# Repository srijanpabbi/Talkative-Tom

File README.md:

# Talkative-Tom
GOTO: https://srijanpabbi.in/projects/#topic_tt
Doc: https://srijanpabbi.blogspot.com/2020/01/talkative-tom.html
Audio storing &amp; playback device with pitch modification using MSP-430 TI-microcontroller / Atmega328P microcontroller, SPI Serial Flash for Storage &amp; class-D amplifier for speaker

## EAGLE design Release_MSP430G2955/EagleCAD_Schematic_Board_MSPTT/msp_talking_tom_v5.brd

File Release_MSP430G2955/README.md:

This is the MSP430 version of this project. For full documentation on Atmega version visit https://srijanpabbi.blogspot.com/2020/01/talkative-tom.html

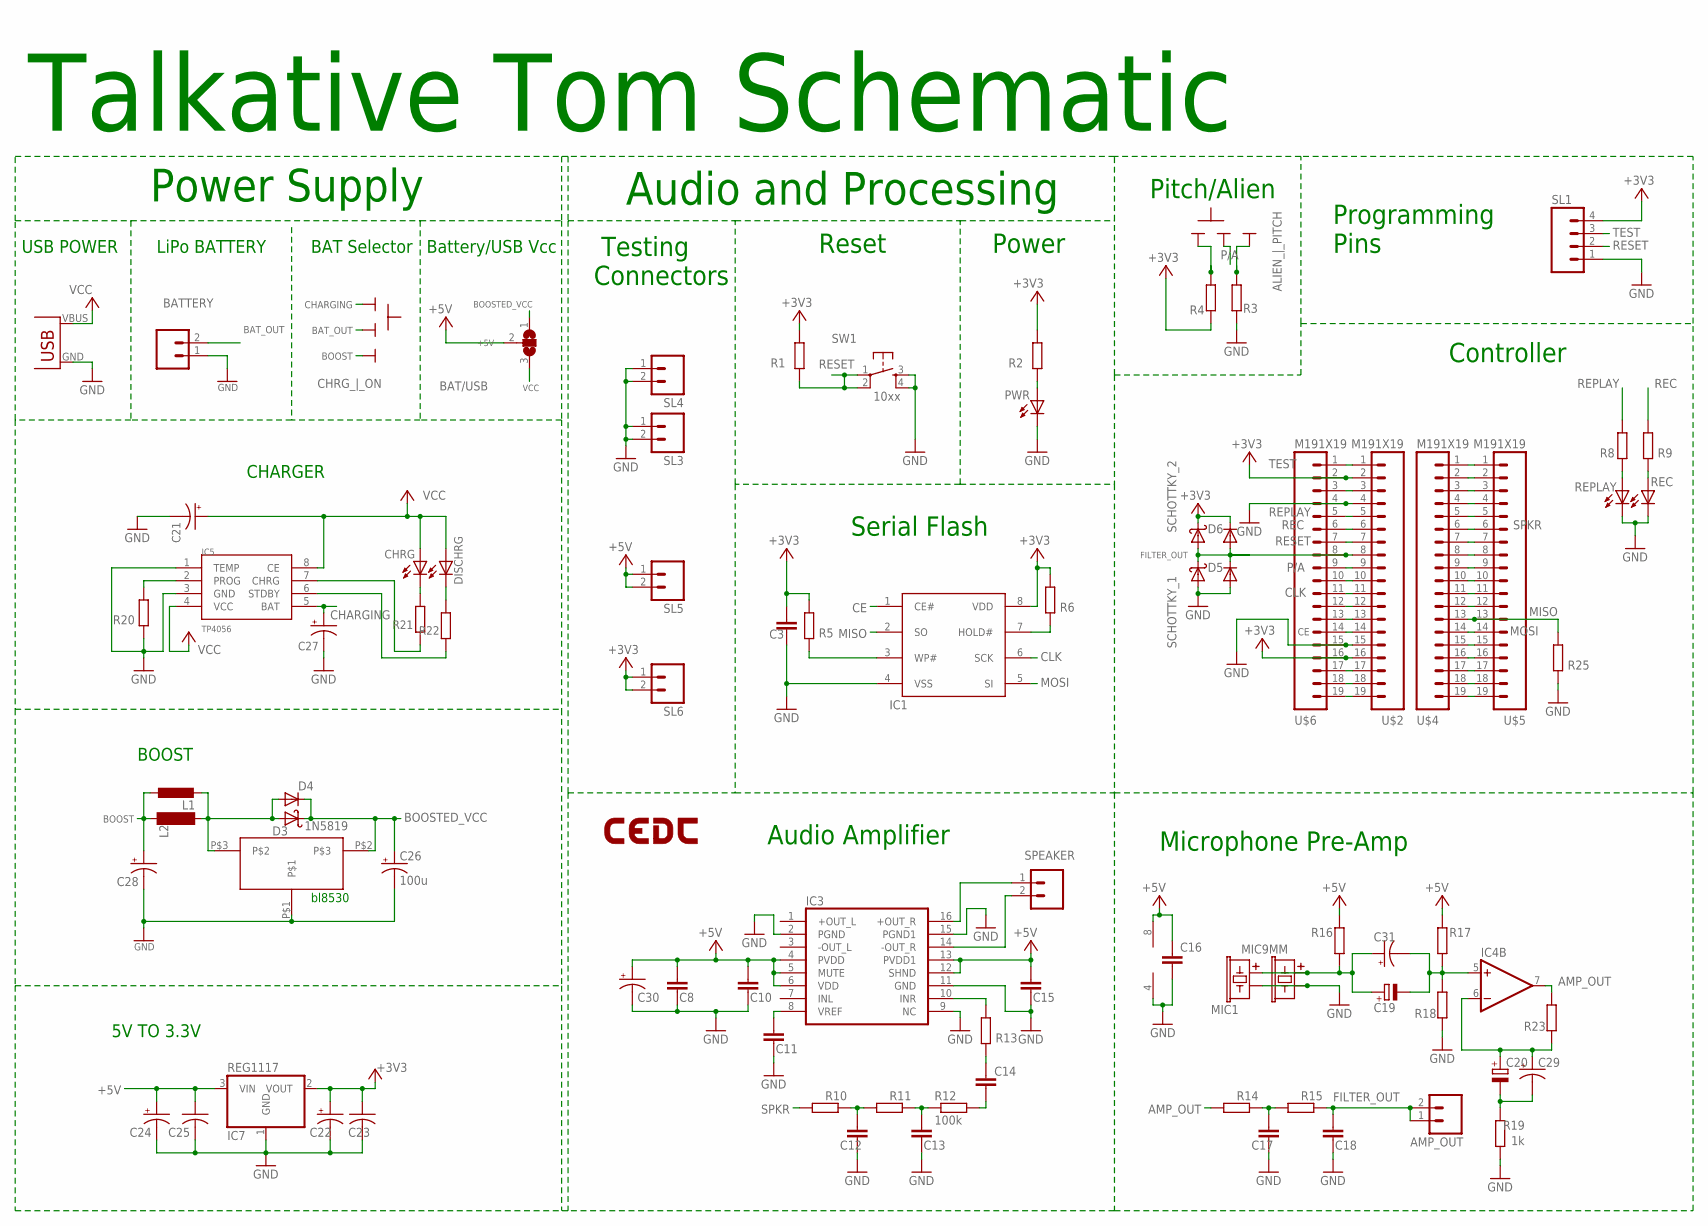
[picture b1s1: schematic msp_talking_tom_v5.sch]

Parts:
ALIEN_|_PITCH: SLIDESWITCH-BIG; BIGSWITCH
AMP_OUT: M02; 02P
BAT/USB: SJ2W; SJ_2
BATTERY: M02JST-PTH-2; 02P
C3, C12, C16, C17, C18, C23, C25: 0.1u; C0805
C8, C10, C15: 1uf; C1206
C11: 0.1uf; C1206
C13: 0.1uf; C0805
C14: 0.47uF; C0603
C19, C20: 10u; E2,5-5
C21, C22, C24, C27, C28, C29, C31: 10u; C/6032-28R
C26: 100u; C/6032-28R
C30: CAP_POL_10V; C/6032-28R
CHRG: LED3MM
CHRG_|_ON: SLIDESWITCH-BIG; BIGSWITCH
D3: 1N5819; DO41-10
D4, D5, D6: DIODE_DIODE-DO214AC; DIODE_DO214AC
DISCHRG: LED3MM
IC1: SST25VF040B_SPI_FLASH; SOIC08
IC3: PAM8403; SOP-16
IC4: LM358N; DIL08
IC5: TP4056; SOP-8
IC6: BL8530_5V
IC7: REG1117; SOT223
L1: L-EUL5650M; L5650M
L2: 47uH; MS85
LOGO2: LOGO-CEDTSILK-18MM; LOGO-CEDT-SILK-18MM
MIC1: MICMIC-4.5MM; MIC-4.5MM
MIC9MM: MIC9.7MM; MIC-9.7MM
PWR: LED3MM
R1, R3, R4, R5, R6, R13, R18, R25: 10k; 0204/7
R2, R8, R9, R19: 1k; 0204/7
R10, R11, R14, R15: 330; 0204/7
R12: 100k; 0204/7
R16: 4.7k; 0204/7
R17, R23: 20k; 0204/7
R20: R-EU_0204/7; 0204/7
R21, R22: 470; 0204/7
REC: LED3MM
REPLAY: LED3MM
SCHOTTKY_1, SCHOTTKY_2: 1N5819; DO41-10
SL1: M04; 04P
SL3, SL4, SL5, SL6: M02; 02P
SPEAKER: M02JST-PTH-VERT; 02P
SW1: 10xx; B3F-10XX
U$1: USB(POWER)
U$2, U$4, U$5, U$6: M191X19; 1X19

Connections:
+3V3: C3.1, C22.+, C23.1, D6.C, IC1.8 (VDD), IC7.2 (VOUT), R1.2, R2.2, R4.2, R5.1, R6.2, SCHOTTKY_2.C, SL1.4, SL6.1, SL6.2, U$2.2, U$2.16, U$6.2, U$6.16
+5V: BAT/USB.2, C8.1, C10.2, C15.2, C16.1, C24.+, C25.1, C30.+, IC3.4 (PVDD), IC3.5 (MUTE), IC3.6 (VDD), IC3.12 (SHND), IC3.13 (PVDD1), IC4.8 (V+), IC7.3 (VIN), R16.2, R17.2, SL5.1, SL5.2
AMP_OUT: IC4.7 (OUT), R14.1, R23.2
AVCC: U$4.16, U$5.16
BAT_OUT: BATTERY.2, CHRG_|_ON.2
BOOST: C28.+, CHRG_|_ON.3, L1.1, L2.1
BOOSTED_VCC: BAT/USB.1, C26.+, D3.C, D4.C, IC6.P$2
CE: IC1.1 (CE#), U$2.14, U$6.14
CHARGING: C27.+, CHRG_|_ON.1, IC5.5 (BAT)
CLK: IC1.6 (SCK), U$2.11, U$6.11
DVCC: U$4.2, U$5.2
FILTER_OUT: AMP_OUT.1, AMP_OUT.2, C18.1, D5.C, D6.A, R15.2, SCHOTTKY_1.C, SCHOTTKY_2.A, U$2.8, U$6.8
GND: BATTERY.1, C3.2, C8.2, C10.1, C11.2, C12.2, C13.2, C15.1, C16.2, C17.2, C18.2, C21.-, C22.-, C23.2, C24.-, C25.2, C26.-, C27.-, C28.-, C30.-, D5.A, IC1.4 (VSS), IC3.2 (PGND), IC3.9 (NC), IC3.11 (GND), IC3.15 (PGND1), IC4.4 (V-), IC5.1 (TEMP), IC5.3 (GND), IC6.P$1, IC7.1 (GND), MIC1.+ (2), MIC9MM.2, PWR.K (C), R3.2, R18.1, R19.1, R20.1, R25.1, REC.K (C), REPLAY.K (C), SCHOTTKY_1.A, SL1.1, SL3.1, SL3.2, SL4.1, SL4.2, SW1.3 (S), SW1.4 (S1), U$1.GND, U$2.4, U$2.15, U$6.4, U$6.15
MICIN1: C13.1, R11.2, R12.1
MISO: IC1.2 (SO), R25.2, U$4.13, U$5.13
MOSI: IC1.5 (SI), U$4.14, U$5.14
unnamed: U$2.3, U$6.3
unnamed: IC1.7 (HOLD#), R6.1
unnamed: IC1.3 (WP#), R5.2
unnamed: U$4.1, U$5.1
unnamed: U$4.15, U$5.15
unnamed: ALIEN_|_PITCH.3, R3.1
unnamed: U$4.4, U$5.4
unnamed: IC3.16 (+OUT_R), SPEAKER.1
unnamed: IC3.14 (-OUT_R), SPEAKER.2
unnamed: C14.2, R13.2
unnamed: IC3.10 (INR), R13.1
unnamed: C12.1, R10.2, R11.1
unnamed: PWR.A, R2.1
unnamed: C17.1, R14.2, R15.1
unnamed: IC5.2 (PROG), R20.2
unnamed: IC5.7 (CHRG), R21.1
unnamed: C14.1, R12.2
unnamed: R8.1, REPLAY.A
unnamed: C11.1, IC3.8 (VREF)
unnamed: ALIEN_|_PITCH.1, R4.1
unnamed: IC5.6 (STDBY), R22.1
unnamed: CHRG.K (C), R21.2
unnamed: DISCHRG.K (C), R22.2
unnamed: D3.A, D4.A, IC6.P$3, L1.2, L2.2
unnamed: C19.+, C31.+, MIC1.- (1), MIC9MM.1, R16.1
unnamed: C19.-, C31.-, IC4.5 (+IN), R17.1, R18.2
unnamed: C20.+, C29.+, IC4.6 (-IN), R23.1
unnamed: R9.2, REC.A
unnamed: U$2.19, U$6.19
unnamed: C20.-, C29.-, R19.2
unnamed: U$2.18, U$6.18
unnamed: U$2.17, U$6.17
unnamed: U$2.13, U$6.13
unnamed: U$2.12, U$6.12
unnamed: U$2.10, U$6.10
unnamed: U$4.3, U$5.3
unnamed: U$4.5, U$5.5
unnamed: U$4.7, U$5.7
unnamed: U$4.8, U$5.8
unnamed: U$4.9, U$5.9
unnamed: U$4.10, U$5.10
unnamed: U$4.11, U$5.11
unnamed: U$4.12, U$5.12
unnamed: U$4.17, U$5.17
unnamed: U$4.18, U$5.18
unnamed: U$4.19, U$5.19
P/A: ALIEN_|_PITCH.2, U$2.9, U$6.9
REC: R9.1, U$2.6, U$6.6
REPLAY: R8.2, U$2.5, U$6.5
RESET: R1.1, SL1.2, SW1.1, SW1.2 (P1), U$2.7, U$6.7
SPKR: R10.1, U$4.6, U$5.6
TEST: SL1.3, U$2.1, U$6.1
VCC: BAT/USB.3, C21.+, CHRG.A, DISCHRG.A, IC5.4 (VCC), IC5.8 (CE), U$1.VBUS (VCC)

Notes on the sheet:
Microphone Pre-Amp
Serial Flash
Reset
Testing Connectors
Controller
Audio Amplifier
Power
Programming Pins
Pitch/Alien
CHARGER
BOOST
5V TO 3.3V
bl8530
USB POWER
LiPo BATTERY
BAT Selector
Battery/USB Vcc
Power Supply
Audio and Processing
Talkative Tom Schematic

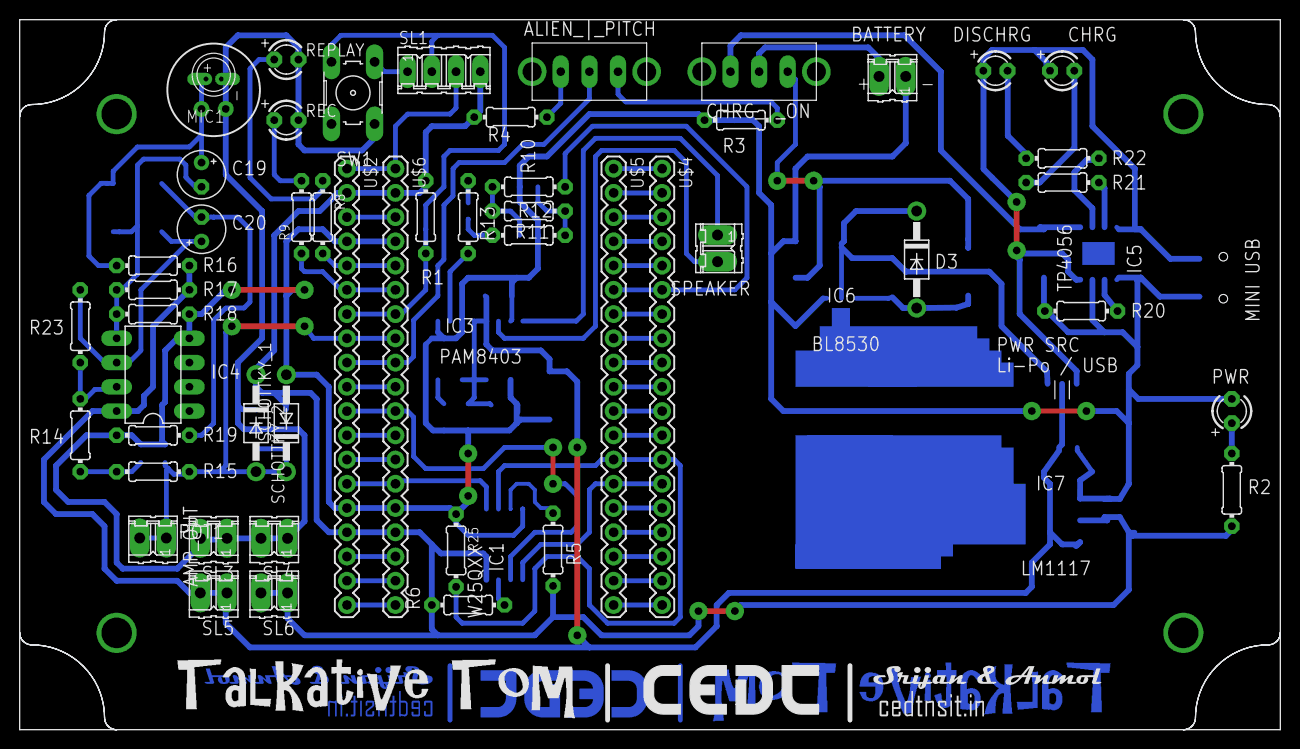
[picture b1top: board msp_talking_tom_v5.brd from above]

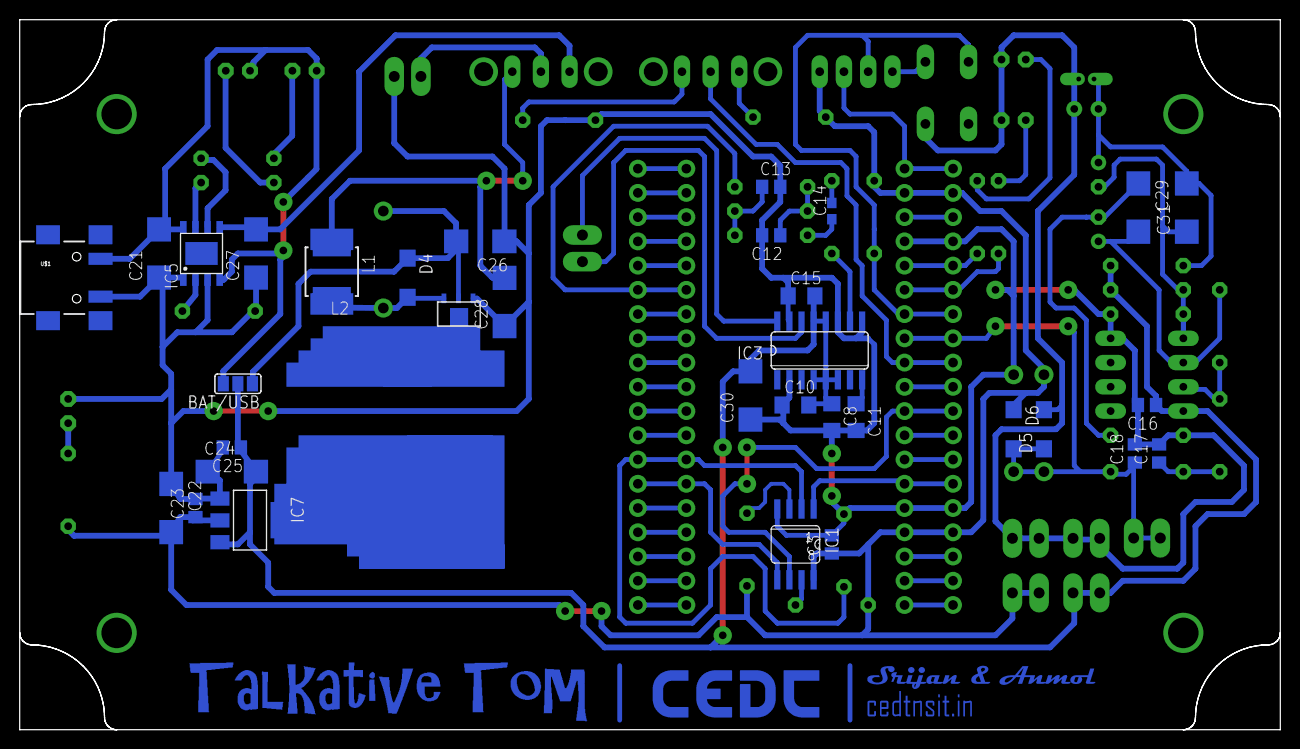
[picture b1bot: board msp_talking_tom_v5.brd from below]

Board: 2 copper layers, 132.1 x 74.4 mm, 86 parts (34 on the bottom side), 69 nets.

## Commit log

2020-12-14 Add files via upload
    adding source code
2020-12-14 Add files via upload
    cad files
2020-12-14 Add files via upload
    caf files atmega

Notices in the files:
parts and their libraries:
SparkFun-Connectors: Licensing: Creative Commons ShareAlike 4.0 International - https://creativecommons.org/licenses/by-sa/4.0
